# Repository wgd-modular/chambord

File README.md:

# Chambord

Chambord is a eurorack module, using the RP2040 or 2350 to implement an
8-channel trigger-in drum sampler.

The 8 channels are laid out **top to bottom = channel 1 to 8**. Each channel
has a trigger input jack and a bicolor (red/green) LED. There is one encoder
(turn + press) and one CV input.

# How to use it

There are only two controls: **turn** the encoder and **press** the encoder.

## Turning the encoder

What turning does depends on the current "page". You step through the pages by
**short-pressing** the encoder:

```
press        press         press        press
SELECT  -->  SAMPLE  -->  VOLUME  -->  PITCH  --> (back to SELECT)
```

- **SELECT** (start here): turn to choose the channel you want to work on.
- **SAMPLE**: turn to change the sample on the selected channel. Each channel
  has 4 samples (banks A–D); turning steps between them.
- **VOLUME**: turn to change the volume of the selected channel.
- **PITCH**: turn to change the pitch of the selected channel.

A short press always advances to the next page and wraps back to SELECT.

## Reading the LEDs

While you're editing, only the **selected channel's** LED lights, colour-coded
by page (green = choosing a thing, amber = setting an amount):

| LED              | Page                                  |
|------------------|---------------------------------------|
| green steady     | SELECT  (turn to pick the channel)    |
| green blinking   | SAMPLE  (turn to change the sample)   |
| amber steady     | VOLUME  (turn to change the volume)   |
| amber blinking   | PITCH   (turn to change the pitch)    |

You'll also hear sample/volume/pitch changes as you turn.

## Screensaver / trigger activity

When you haven't touched the encoder for about **10 seconds**, the row switches
to a trigger-activity display: every channel flashes **green** when it gets a
trigger. Touch the encoder and it goes back to showing what you're editing.
(This keeps trigger flashes from distracting you while you work.)

## CV input

**Long-press** the encoder (hold ~3/4 second) to assign the CV input to the
**volume** of the currently selected channel. Long-press again on the same
channel to turn CV off.

## Settings are saved

Your per-channel sample and pitch choices (and the CV assignment) are saved
automatically to flash a moment after you stop adjusting, and restored on the
next power-up. Saving only happens while nothing is sounding, so it never
interrupts playback.

## If the encoder turns the wrong way

Open `firmware/Pikobeats/Pikobeats.ino` and change `ENCODER_DIR` from `1` to
`-1` (near the top), then rebuild.

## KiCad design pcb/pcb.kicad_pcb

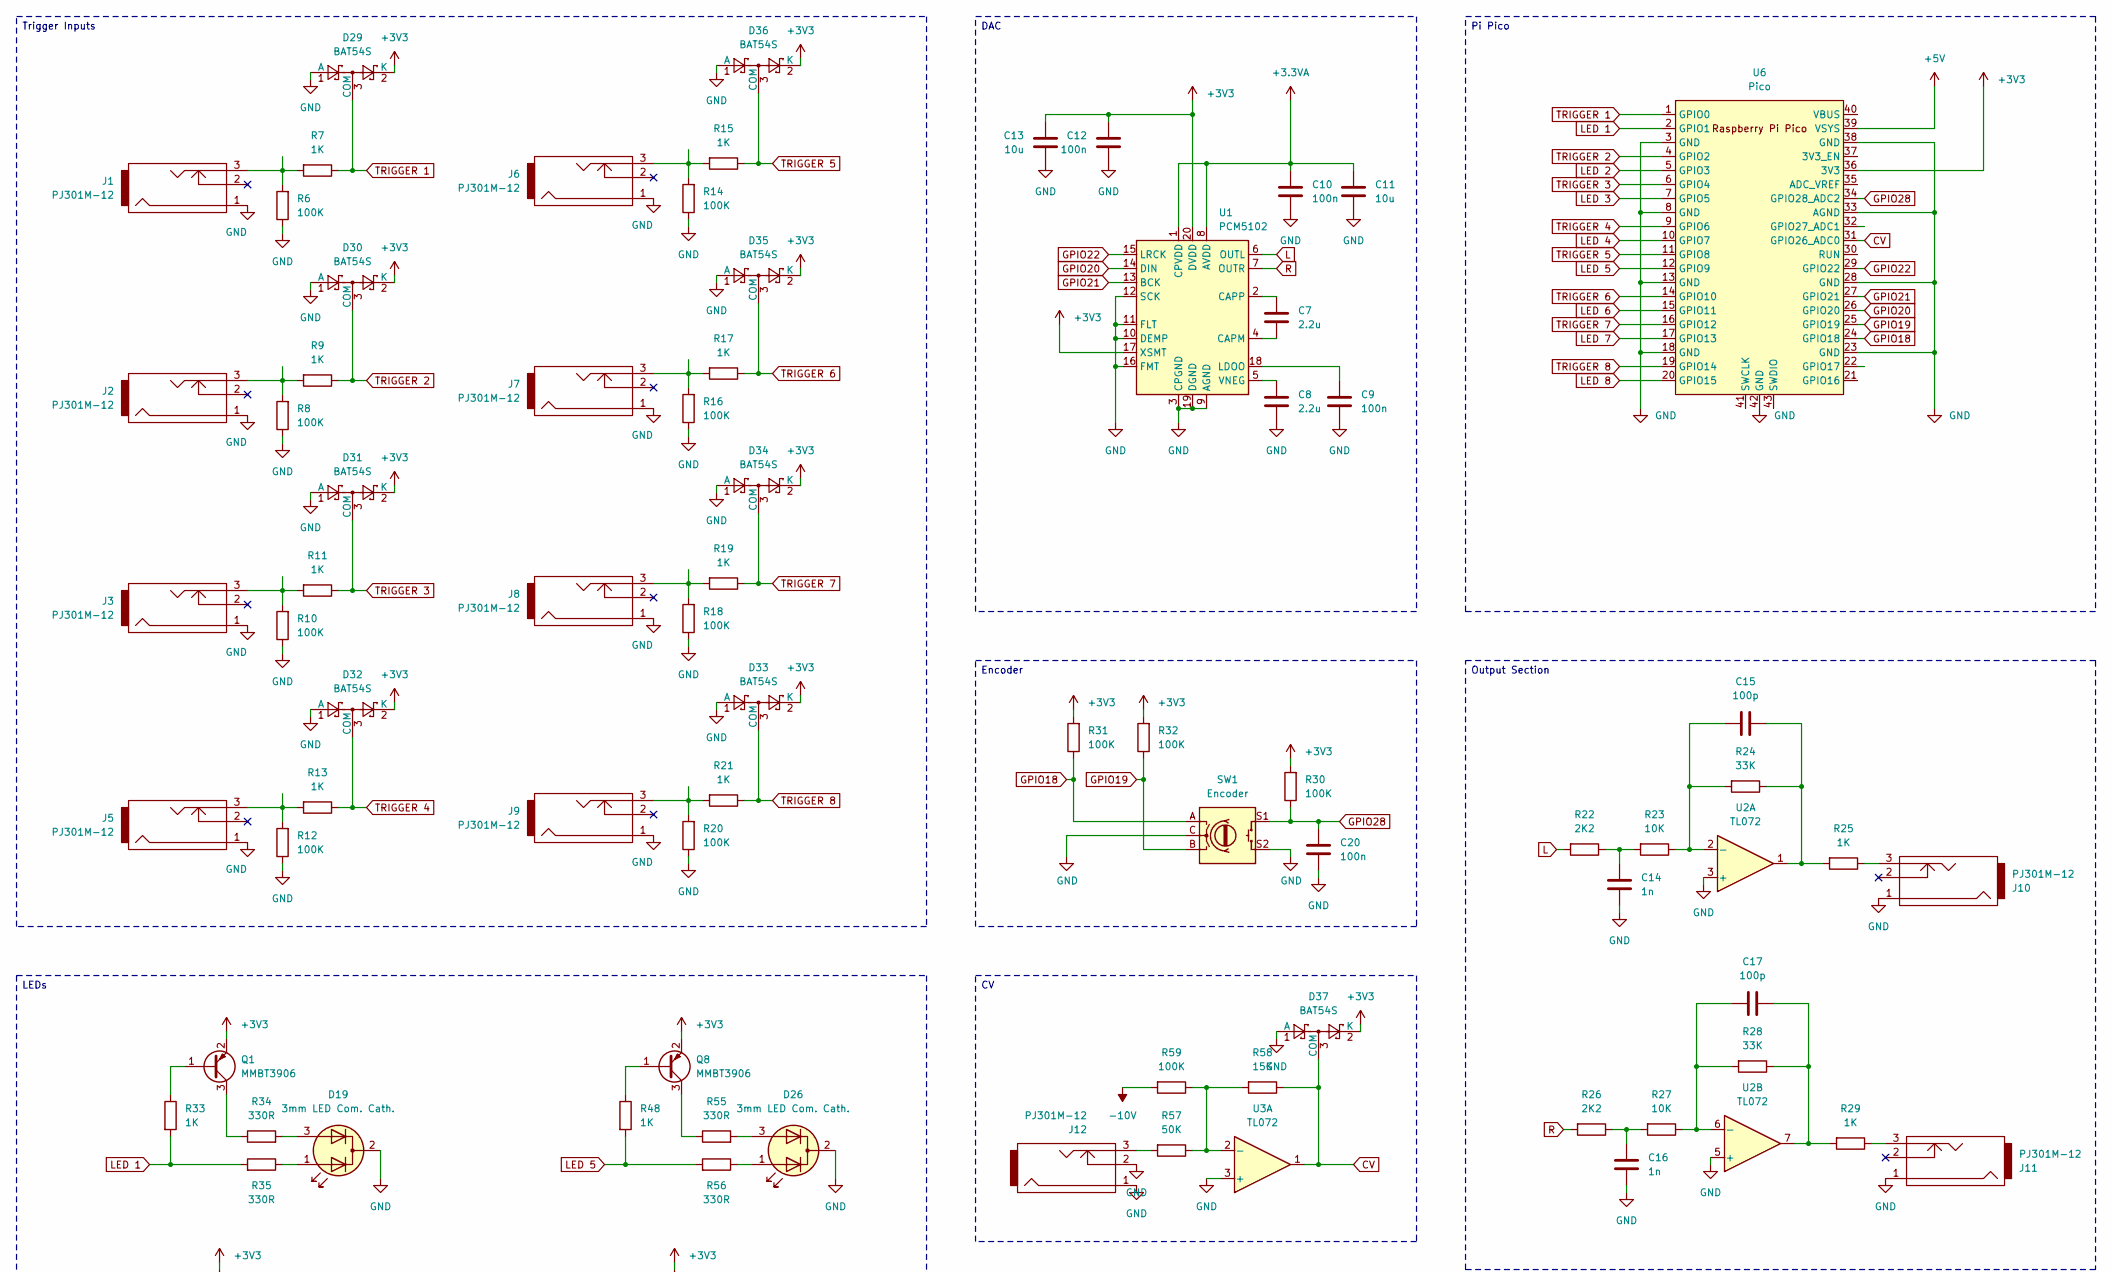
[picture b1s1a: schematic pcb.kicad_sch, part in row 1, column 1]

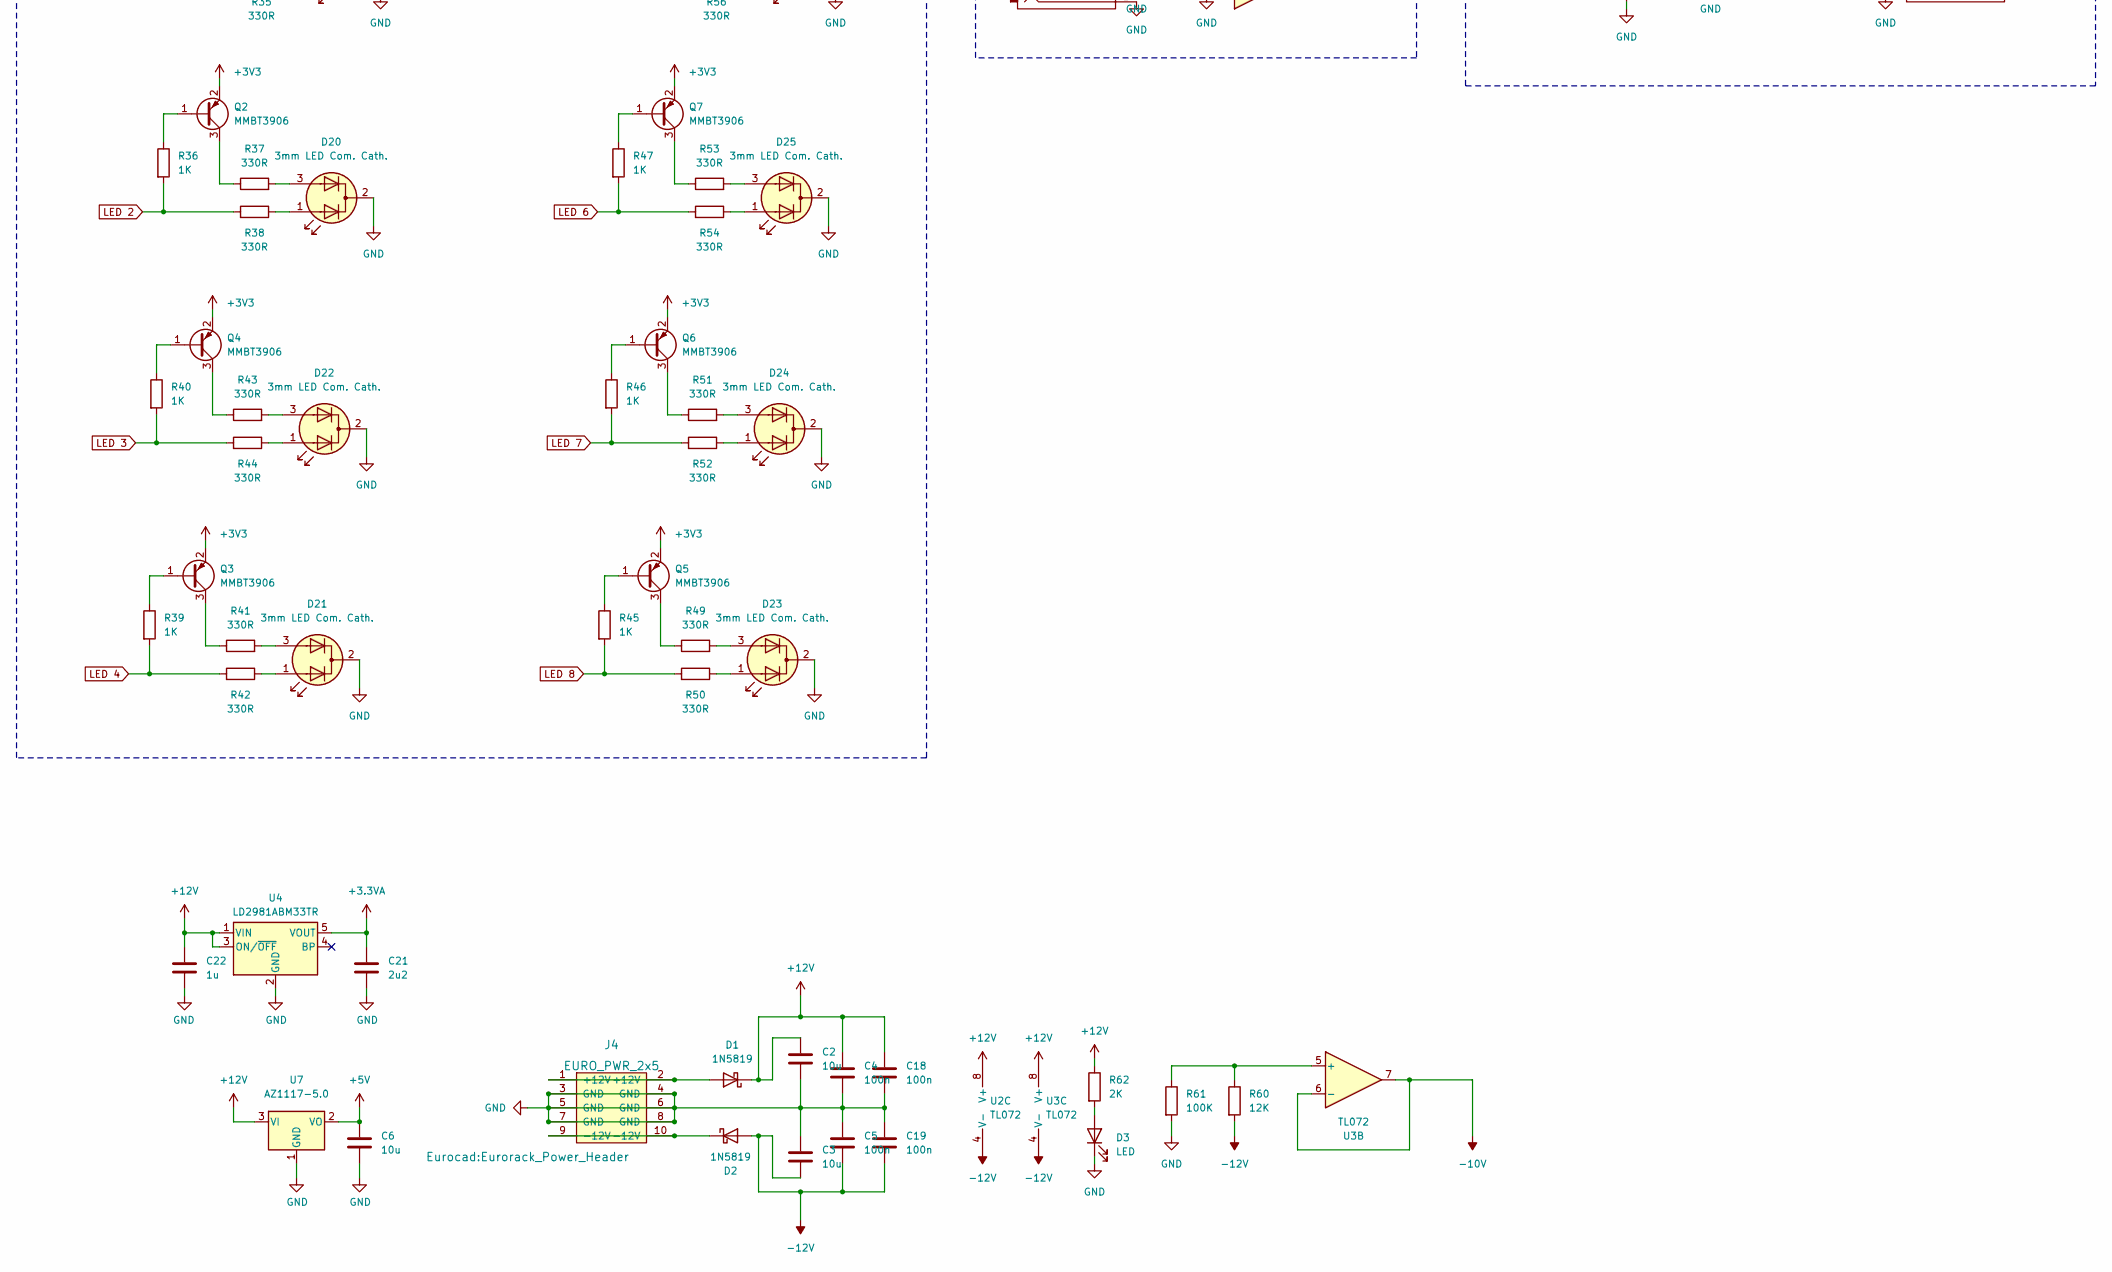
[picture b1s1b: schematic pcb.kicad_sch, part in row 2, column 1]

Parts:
C2, C3, C6, C11, C13: 10u; C_0805_2012Metric
C4, C5, C9, C10, C12, C18, C19, C20: 100n; C_0603_1608Metric
C7, C8: 2.2u; C_0805_2012Metric
C14, C16: 1n; C_0603_1608Metric
C15, C17: 100p; C_0603_1608Metric
C21: 2u2; C_0805_2012Metric
C22: 1u; C_0805_2012Metric
D1, D2: 1N5819; D_SOD-123
D3: LED; LED_0603_1608Metric
D19, D20, D21, D22, D23, D24, D25, D26: 3mm LED Com. Cath.; LED_D3.0mm-3
D29, D30, D31, D32, D33, D34, D35, D36, D37: BAT54S; SOT-23; JLC C7420333
J1, J2, J3, J5, J6, J7, J8, J9, J10, J11, J12: PJ301M-12
J4: EURO_PWR_2x5; Eurorack_Power_Header
Q1, Q2, Q3, Q4, Q5, Q6, Q7, Q8: MMBT3906; SOT-23
R6, R8, R10, R12, R14, R16, R18, R20, R30, R31, R32, R59, R61: 100K; R_0603_1608Metric
R7, R9, R11, R13, R15, R17, R19, R21, R25, R29, R33, R36, R39, R40, R45, R46, R47, R48: 1K; R_0603_1608Metric
R22, R26: 2K2; R_0603_1608Metric
R23, R27: 10K; R_0603_1608Metric
R24, R28: 33K; R_0603_1608Metric
R34, R35, R37, R38, R41, R42, R43, R44, R49, R50, R51, R52, R53, R54, R55, R56: 330R; R_0603_1608Metric
R57: 50K; R_0603_1608Metric
R58: 15K; R_0603_1608Metric
R60: 12K; R_0603_1608Metric
R62: 2K; R_0603_1608Metric
SW1: Encoder; RotaryEncoder_Alps_EC11E-Switch_Vertical_H20mm
U1: PCM5102; TSSOP-20_4.4x6.5mm_P0.65mm
U2, U3: TL072; SOIC-8_3.9x4.9mm_P1.27mm
U4: LD2981ABM33TR; SOT-23-5
U6: Pico; RaspberryPi_Pico_Common_THT
U7: AZ1117-5.0; SOT-223-3_TabPin2

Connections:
+3.3VA: C10.1, C11.1, C21.1, U1.1 (CPVDD), U1.8 (AVDD), U4.5 (VOUT)
+3V3: C12.1, C13.1, D29.2 (K), D30.2 (K), D31.2 (K), D32.2 (K), D33.2 (K), D34.2 (K), D35.2 (K), D36.2 (K), D37.2 (K), Q1.2 (E), Q2.2 (E), Q3.2 (E), Q4.2 (E), Q5.2 (E), Q6.2 (E), Q7.2 (E), Q8.2 (E), R30.2, R31.2, R32.2, U1.17 (XSMT), U1.20 (DVDD), U6.36 (3V3)
+5V: C6.1, U6.39 (VSYS), U7.2 (VO)
+12V: C2.1, C4.1, C18.1, C22.1, D1.1 (K), R62.1, U2.8 (V+), U3.8 (V+), U4.1 (VIN), U4.3 (ON/~OFF), U7.3 (VI)
-10V: R59.2, U3.6 (-), U3.7
-12V: C3.2, C5.2, C19.2, D2.2 (A), R60.2, U2.4 (V-), U3.4 (V-)
CV: D37.3 (COM), R58.1, U3.1, U6.31 (GPIO26_ADC0)
GND: C2.2, C3.1, C4.2, C5.1, C6.2, C8.2, C9.2, C10.2, C11.2, C12.2, C13.2, C14.2, C16.2, C18.2, C19.1, C20.2, C21.2, C22.2, D3.1 (K), D19.2 (K), D20.2 (K), D21.2 (K), D22.2 (K), D23.2 (K), D24.2 (K), D25.2 (K), D26.2 (K), D29.1 (A), D30.1 (A), D31.1 (A), D32.1 (A), D33.1 (A), D34.1 (A), D35.1 (A), D36.1 (A), D37.1 (A), J1.1, J2.1, J3.1, J4.3 (GND), J4.4 (GND), J4.5 (GND), J4.6 (GND), J4.7 (GND), J4.8 (GND), J5.1, J6.1, J7.1, J8.1, J9.1, J10.1, J11.1, J12.1, J12.2, R6.1, R8.1, R10.1, R12.1, R14.1, R16.1, R18.1, R20.1, R61.2, SW1.C, SW1.S2, U1.3 (CPGND), U1.9 (AGND), U1.10 (DEMP), U1.11 (FLT), U1.12 (SCK), U1.16 (FMT), U1.19 (DGND), U2.3 (+), U2.5 (+), U3.3 (+), U4.2 (GND), U6.3 (GND), U6.8 (GND), U6.13 (GND), U6.18 (GND), U6.23 (GND), U6.28 (GND), U6.33 (AGND), U6.38 (GND), U6.42 (GND), U7.1 (GND)
GPIO18: R31.1, SW1.A, U6.24 (GPIO18)
GPIO19: R32.1, SW1.B, U6.25 (GPIO19)
GPIO20: U1.14 (DIN), U6.26 (GPIO20)
GPIO21: U1.13 (BCK), U6.27 (GPIO21)
GPIO22: U1.15 (LRCK), U6.29 (GPIO22)
GPIO28: C20.1, R30.1, SW1.S1, U6.34 (GPIO28_ADC2)
L: R22.2, U1.6 (OUTL)
LED 1: R33.2, R35.2, U6.2 (GPIO1)
LED 2: R36.2, R38.2, U6.5 (GPIO3)
LED 3: R40.2, R44.2, U6.7 (GPIO5)
LED 4: R39.2, R42.2, U6.10 (GPIO7)
LED 5: R48.2, R56.2, U6.12 (GPIO9)
LED 6: R47.2, R54.2, U6.15 (GPIO11)
LED 7: R46.2, R52.2, U6.17 (GPIO13)
LED 8: R45.2, R50.2, U6.20 (GPIO15)
unnamed: C14.1, R22.1, R23.2
unnamed: C15.2, R24.1, R25.2, U2.1
unnamed: C16.1, R26.1, R27.2
unnamed: C17.2, R28.1, R29.2, U2.7
unnamed: D1.2 (A), J4.1 (+12V), J4.2 (+12V)
unnamed: D2.1 (K), J4.9 (-12V), J4.10 (-12V)
unnamed: D3.2 (A), R62.2
unnamed: D19.1 (A1), R35.1
unnamed: D19.3 (A2), R34.2
unnamed: D20.1 (A1), R38.1
unnamed: D20.3 (A2), R37.2
unnamed: D21.1 (A1), R42.1
unnamed: D21.3 (A2), R41.2
unnamed: D22.1 (A1), R44.1
unnamed: D22.3 (A2), R43.2
unnamed: D23.1 (A1), R50.1
unnamed: D23.3 (A2), R49.2
unnamed: D24.1 (A1), R52.1
unnamed: D24.3 (A2), R51.2
unnamed: D25.1 (A1), R54.1
unnamed: D25.3 (A2), R53.2
unnamed: D26.1 (A1), R56.1
unnamed: D26.3 (A2), R55.2
unnamed: J1.3, R6.2, R7.2
unnamed: J2.3, R8.2, R9.2
unnamed: J3.3, R10.2, R11.2
unnamed: J5.3, R12.2, R13.2
unnamed: J6.3, R14.2, R15.2
unnamed: J7.3, R16.2, R17.2
unnamed: J8.3, R18.2, R19.2
unnamed: J9.3, R20.2, R21.2
unnamed: J10.3, R25.1
unnamed: J11.3, R29.1
unnamed: J12.3, R57.2
unnamed: Q1.1 (B), R33.1
unnamed: Q1.3 (C), R34.1
unnamed: Q2.1 (B), R36.1
unnamed: Q2.3 (C), R37.1
unnamed: Q3.1 (B), R39.1
unnamed: Q3.3 (C), R41.1
unnamed: Q4.1 (B), R40.1
unnamed: Q4.3 (C), R43.1
unnamed: Q5.1 (B), R45.1
unnamed: Q5.3 (C), R49.1
unnamed: Q6.1 (B), R46.1
unnamed: Q6.3 (C), R51.1
unnamed: Q7.1 (B), R47.1
unnamed: Q7.3 (C), R53.1
unnamed: Q8.1 (B), R48.1
unnamed: Q8.3 (C), R55.1
unnamed: C7.2, U1.4 (CAPM)
unnamed: C7.1, U1.2 (CAPP)
unnamed: C9.1, U1.18 (LDOO)
unnamed: C8.1, U1.5 (VNEG)
unnamed: C15.1, R23.1, R24.2, U2.2 (-)
unnamed: C17.1, R27.1, R28.2, U2.6 (-)
unnamed: R57.1, R58.2, R59.1, U3.2 (-)
unnamed: R60.1, R61.1, U3.5 (+)
R: R26.2, U1.7 (OUTR)
TRIGGER 1: D29.3 (COM), R7.1, U6.1 (GPIO0)
TRIGGER 2: D30.3 (COM), R9.1, U6.4 (GPIO2)
TRIGGER 3: D31.3 (COM), R11.1, U6.6 (GPIO4)
TRIGGER 4: D32.3 (COM), R13.1, U6.9 (GPIO6)
TRIGGER 5: D36.3 (COM), R15.1, U6.11 (GPIO8)
TRIGGER 6: D35.3 (COM), R17.1, U6.14 (GPIO10)
TRIGGER 7: D34.3 (COM), R19.1, U6.16 (GPIO12)
TRIGGER 8: D33.3 (COM), R21.1, U6.19 (GPIO14)

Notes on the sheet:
Encoder
DAC
LEDs
Pi Pico
Trigger Inputs
Output Section

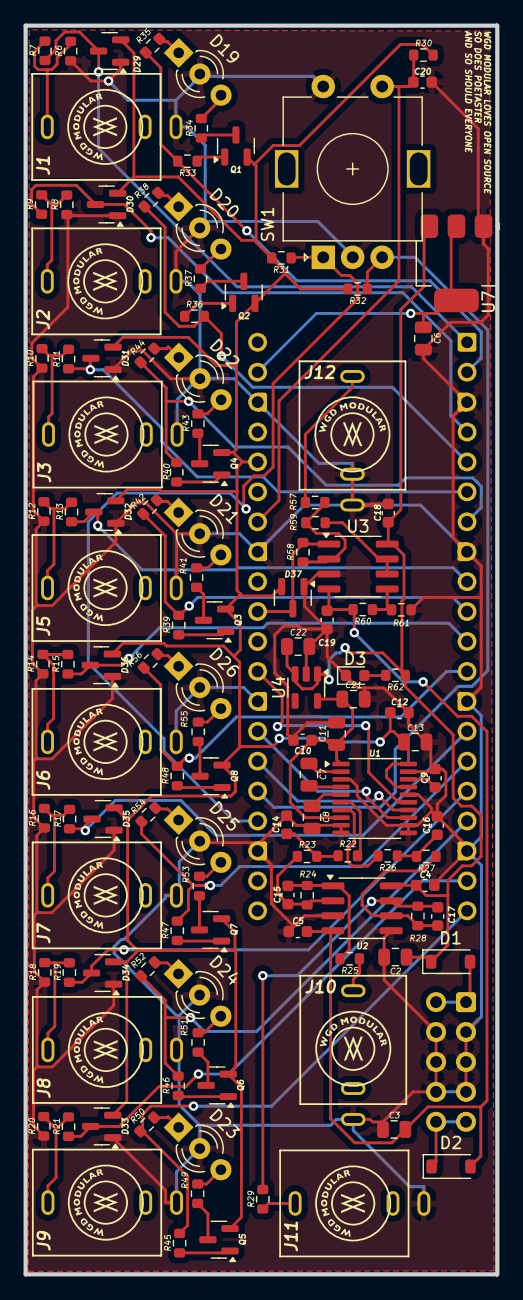
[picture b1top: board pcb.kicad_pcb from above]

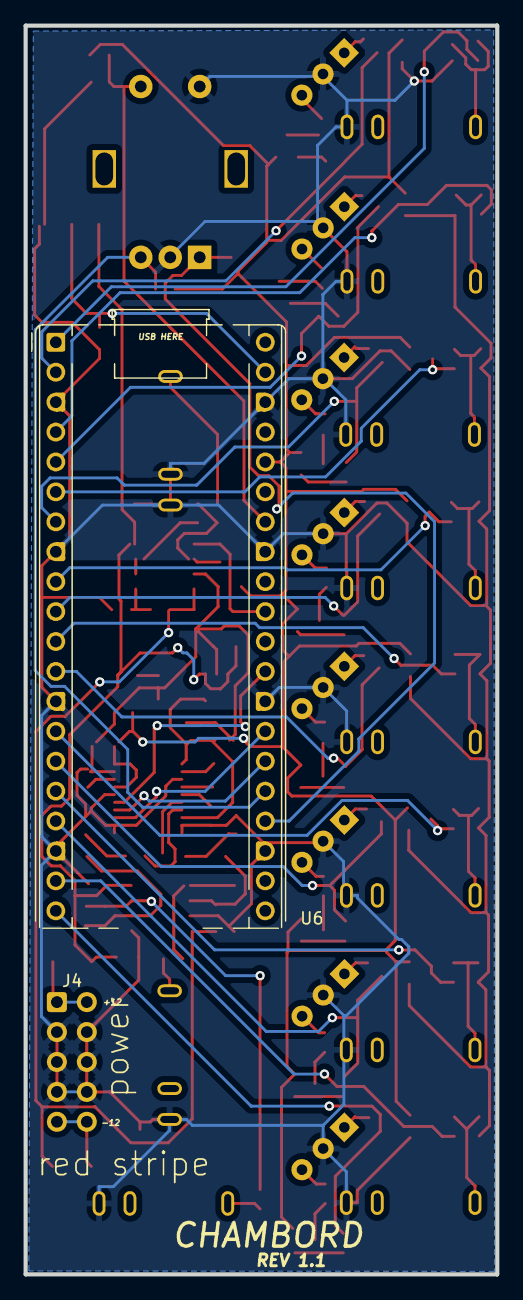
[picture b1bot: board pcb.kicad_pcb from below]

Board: 2 copper layers, 40.0 x 106.0 mm, 125 parts (2 on the bottom side), 90 nets.

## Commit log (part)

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2025-04-16 Start schematic
2025-04-17 Continue schematic
2025-04-17 Add LEDs, Triggers and CV in (closes #1)
2025-04-19 Replace OP-Amp and add GPIO input protection diodes for eventual clamping
2025-05-01 Implement feedback from Niek
2025-05-04 Rev 1
2025-05-04 Move U7
2025-06-13 Fix missing XSMT connection to 3V3
2025-06-19 Add: firmware directory
2025-06-19 Add: test firmware for leds and i2s
2025-06-19 Add: Readme
2025-06-19 Add: timers
2025-06-19 Refactor: trim all functions to chambord interfaces
2025-06-19 Fix: get all the basics running
2025-06-19 Debug: still using the leds to test some state.
2025-06-20 Fix. both pitch shift and sample select working
2025-06-20 Add. two kits
2025-06-20 Fix: remove core idling since it can crash.
2025-06-20 Fix: move encoder processing and remove contention on leds to remove noise
2025-06-20 Add: cv input to volume of current track, mode 0
2025-06-20 Add: initial release candidate
2025-06-20 Fix: move jack in led signal to timer. cv also on slow timer.
2025-06-20 Fix: corrected uf2
2025-06-26 Fix 3V3 missing on DAC and use additional LDO for 3V3 on DAC
2025-06-28 Add: higher quality acoustic
2025-06-28 Fix: move DAC writes to 48khz timer and only do sample generation on request when dac has been writtern.
2025-06-28 Fix: new uf2 with latest timer code
2025-07-06 Rev 1.1
2025-07-23 Refactor: red/green duty cycles (red on by default, flipped in software).
2025-07-23 Refactor: add a 4 part kit, update ui and control
2025-07-23 Docs: update readme with some ui documentation
2025-07-24 Refactor: move led indicators to current channel
2025-07-29 fix: Allow rotational channel selection
2025-08-22 Add: techno 4 kits
2025-08-22 Add: readme for production notes
2025-08-22 Update: test 44khz 16 bit h
2025-12-08 Update: edited samples, all 16bit, 44khz
2025-12-10 Fix: set to 44100 kHz for pitch correct play, up buffer lengths
2026-06-10 [Add] new kit for chambord
2026-06-10 [Add] built uf2 for the folk
2026-06-27 feat: rework audio engine, simplify UI, add CI
    Audio:
    - render on core1 paced by the I2S DMA buffer instead of a timer ISR
    - soft-clip the mix for headroom, precompute per-voice gain, ramp attacks
    - fix constrain() no-ops, the interpolation read past the sample end and
    the off-by-one LED and trigger loop bounds
    UI:
2026-06-29 [Fix] remove the unused running average code since it is not applicable
2026-06-29 [Fix] remove unused encoder button tracking
2026-06-29 Add a block to detect 3 states * longpress on onPressed * double click on release * after timeouts, single click
    The save method is called from within double click confirm.
2026-06-30 [Fix] set screensaver back to somewhat longer time. reduce debounce interval for faster double clicks
2026-06-30 [Fix] cleanup, move doc notes, add note about unused code
2026-06-30 [Fix] remove uneeded code
